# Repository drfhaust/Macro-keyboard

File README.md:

# Macro Keyboard

**Macro Keyboard with ESP32-S3**

This repository contains the design and code for building a custom macro keyboard powered by the ESP32-S3 microcontroller.

## Overview

- **Design**: A macro keyboard with customizable keys and LEDs for different functionalities.
- **Microcontroller**: Powered by the ESP32-S3 with a built-in touch screen and additional hardware components.
- **Customization**: Supports custom key mappings and macros via a JSON configuration.
- **Hardware Design**: The keyboard's hardware is modular, making it adaptable for various input needs.

## Hardware Specifications

- **Microcontroller**: ESP32-S3 with built-in wireless connectivity.
- **Key Components**: Uses Cherry MX-compatible key switches.
- **LEDs**: Individually addressable RGB LEDs for customizable lighting.
- **Screen**: Touch-enabled screen for additional control and feedback.
- **Battery**: Supports external power, and can be adapted for battery-powered use.
- **Charging**: USB Type-C port for charging and data transfer.
- **Connection**: Supports both wired and wireless communication with a host device.

## Software Features

- **Macro Management**: The macros can be configured through the `button.json` file, where each button is assigned a specific action or macro.
- **LED Control**: RGB LEDs can be customized for each button based on the configuration.
- **Key Mapping**: Easily programmable for various applications, from simple shortcuts to complex multi-step macros.
- **Python Integration**: Python scripts are provided to manage macro configurations and interface with the hardware.

## Power Details

- **Power Input**: Powered through USB Type-C or battery.
- **Power Consumption**: Optimized for low power consumption during idle states.

## Repository Structure

- **Arduino code**: Contains the LVGL porting for the ESP32-S3 along with the Arduino source code for the project.
  - `lvgl_Porting`: Core source files for integrating LVGL (LittlevGL) with the ESP32-S3.
  
- **Macro keyboard**: Includes hardware designs, PCB schematics, and component configurations.
  - `GERBER`: Files for manufacturing the PCB.
  - `custom components`: KiCad components for custom parts used in the keyboard.
  - `backups`: Backup files for the PCB designs.

- **python code**: Python scripts to manage macros and configure button functionalities.
  - `macro_manager_v4.py`: Python script for managing the macro functions of the keyboard.
  
- **solidwork 3d**: 3D models of the keyboard parts, including key switches and case designs.
  
- **button.json**: Configuration file where button mappings and LED colors are stored.

## Getting Started

1. **Clone this repository**:
   ```bash
   git clone <repository-url>
   ```

2. **Hardware Setup**: 
   - Flash the ESP32-S3 with the code in `Arduino code/lvgl_Porting`.
   - Assemble the PCB and components according to the schematics in the `Macro keyboard` folder.

3. **Software Setup**:
   - Install the required Python libraries by running:
     ```bash
     pip install -r requirements.txt
     ```

4. **Macro Management**:
   - Configure macros by editing `button.json`.
   - Run the macro manager script to apply your changes:
     ```bash
     python python code/v4/macro_manager_v4.py
     ```

## Contributing

Please read the contribution guidelines before making any changes.

## License

This project is licensed under the MIT License.

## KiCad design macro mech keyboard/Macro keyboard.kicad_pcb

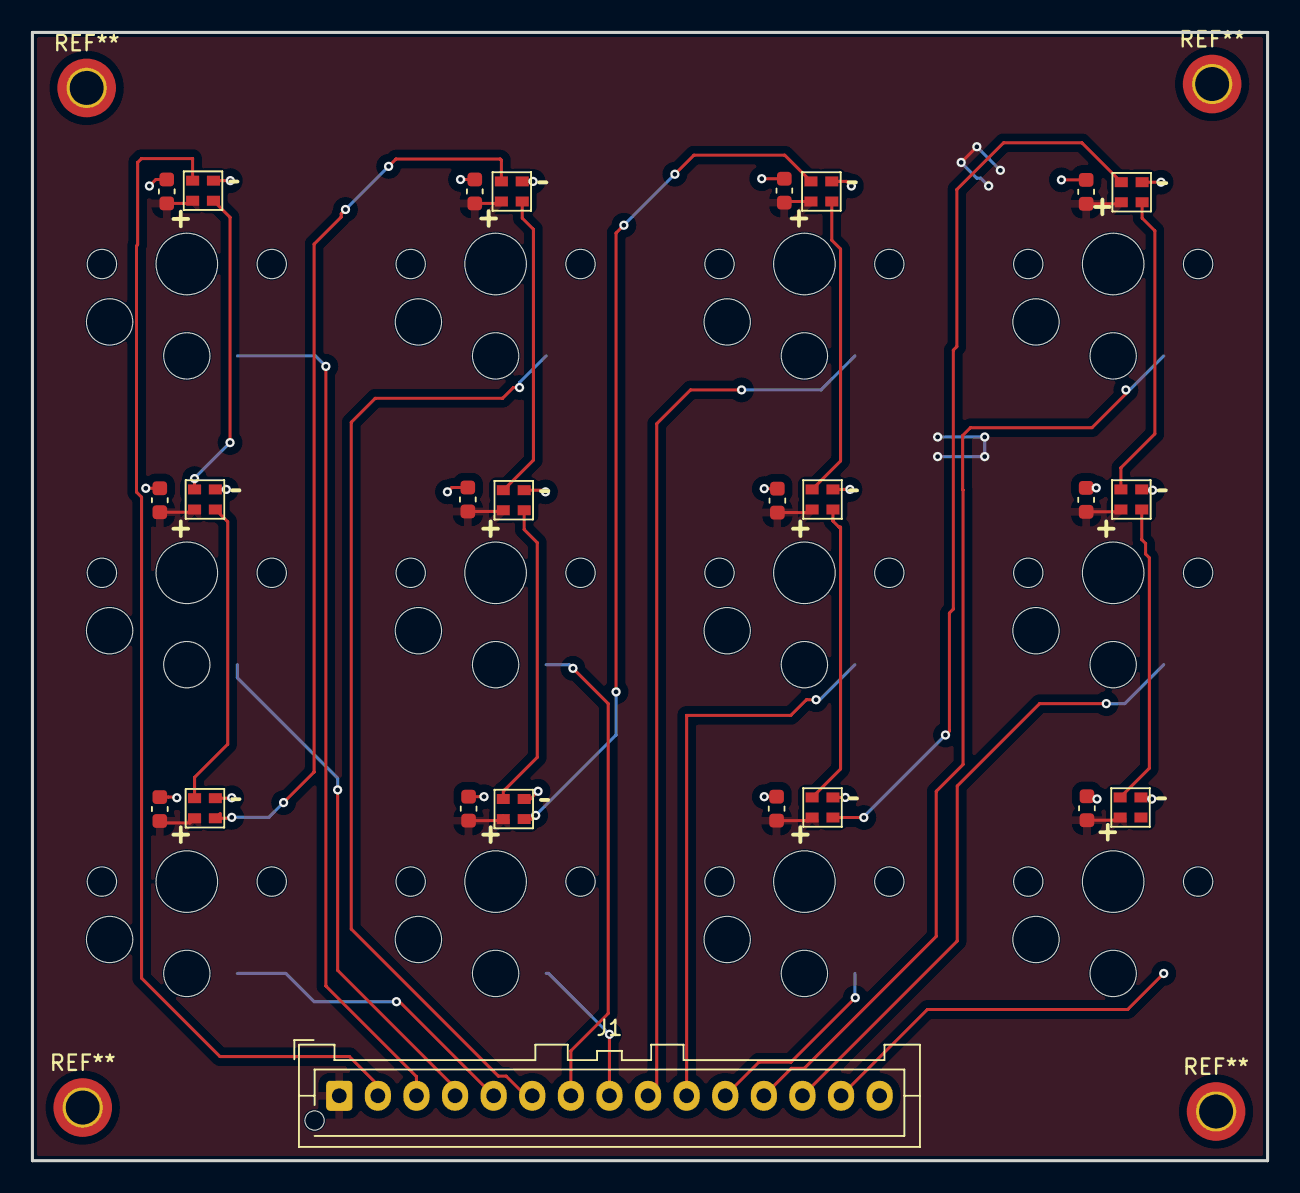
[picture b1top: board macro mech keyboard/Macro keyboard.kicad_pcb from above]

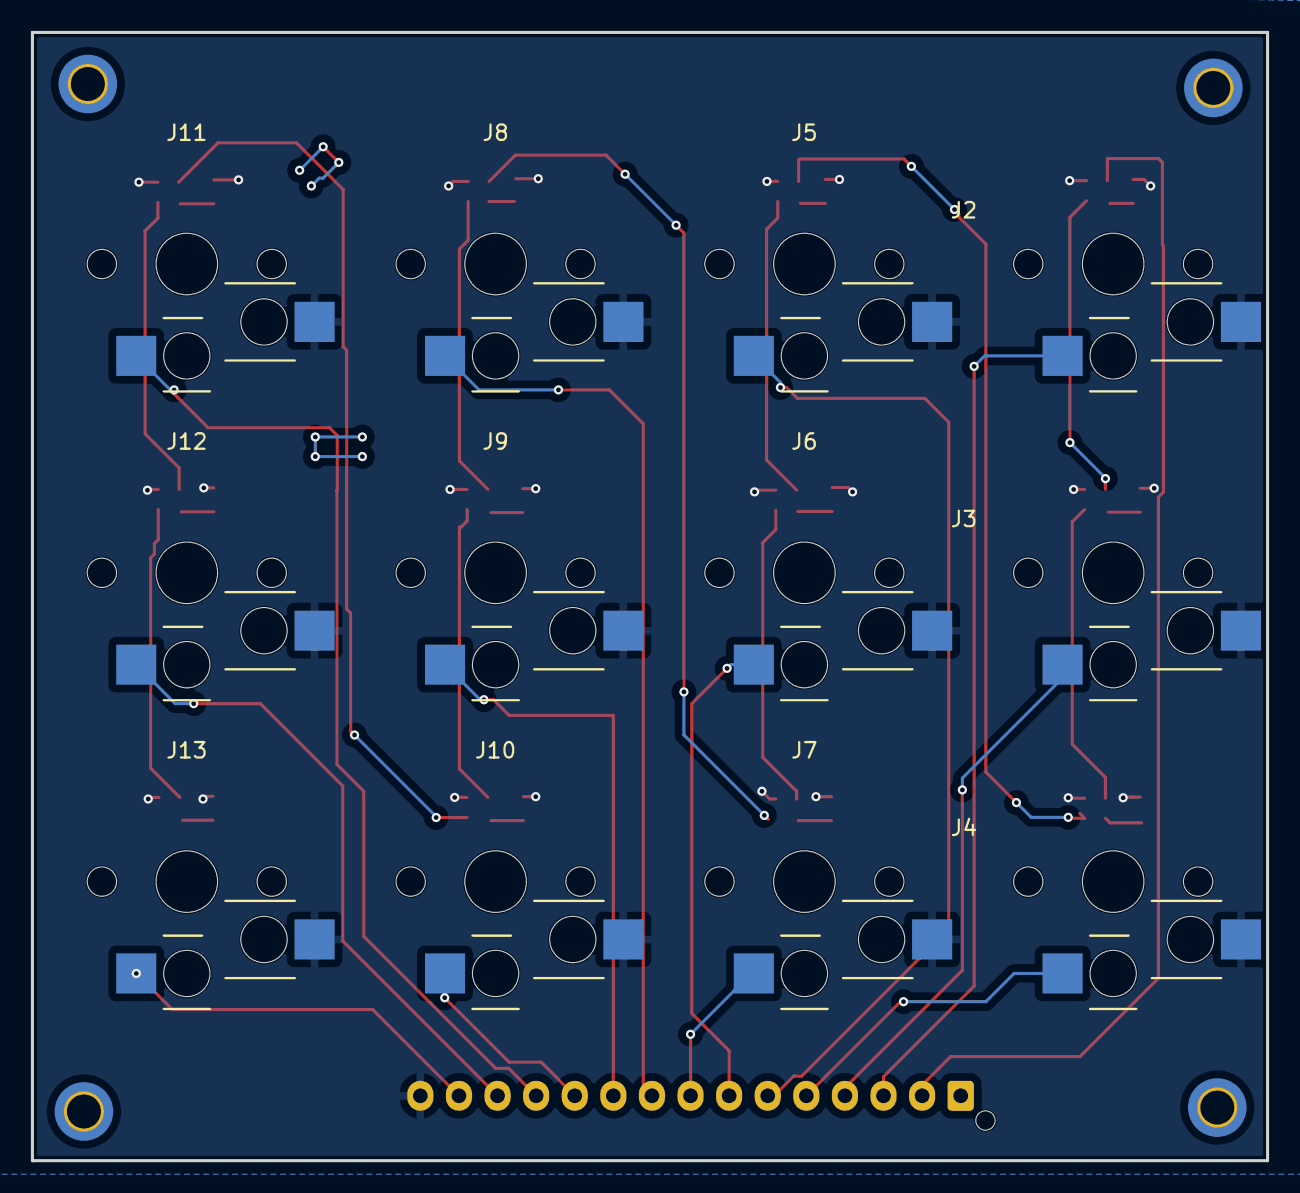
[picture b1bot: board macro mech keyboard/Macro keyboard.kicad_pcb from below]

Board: 2 copper layers, 80.0 x 73.1 mm, 37 parts (12 on the bottom side), 26 nets.

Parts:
C13, C14, C15, C16, C17, C18, C19, C20, C21, C22, C23, C24: 100n; C_0603_1608Metric
D2, D3, D4, D5, D6, D7, D8, D9, D10, D11, D12, D13: RGB; LED_SMD_XINGLIGHT_XL-2020RGBC-WS2812B
J1: Conn_01x15_Pin; JST_XA_B15B-XASK-1-A_1x15_P2.50mm_Vertical
J2, J3, J4, J5, J6, J7, J8, J9, J10, J11, J12, J13: CPG135001S30; Connector_Keyswitch_Socket_KAILH_CPG135001S30

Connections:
+3.3V: C13.1, C14.1, C15.1, C16.1, C17.1, C18.1, C19.1, C20.1, C21.1, C22.1, C23.1, C24.1, D2.4 (vdd), D3.4 (vdd), D4.4 (vdd), D5.4 (vdd), D6.4 (vdd), D7.4 (vdd), D8.4 (vdd), D9.4 (vdd), D10.4 (vdd), D11.4 (vdd), D12.4 (vdd), D13.4 (vdd), J1.1
/BUTTON1: J1.3, J2.1
/BUTTON2: J1.4, J3.1
/BUTTON3: J1.5, J4.1
/BUTTON4: J1.6, J5.1
/BUTTON5: J1.7, J6.1
/BUTTON6: J1.8, J7.1
/BUTTON7: J1.9, J8.1
/BUTTON8: J1.10, J9.1
/BUTTON9: J1.11, J10.1
/BUTTON10: J1.12, J11.1
/BUTTON11: J1.13, J12.1
/BUTTON12: J1.14, J13.1
/RGBLED: D2.3 (di), J1.2
/RGBc: D7.1 (do), D8.3 (di)
GND: C13.2, C14.2, C15.2, C16.2, C17.2, C18.2, C19.2, C20.2, C21.2, C22.2, C23.2, C24.2, D2.2 (gnd), D3.2 (gnd), D4.2 (gnd), D5.2 (gnd), D6.2 (gnd), D7.2 (gnd), D8.2 (gnd), D9.2 (gnd), D10.2 (gnd), D11.2 (gnd), D12.2 (gnd), D13.2 (gnd), J1.15, J2.2, J3.2, J4.2, J5.2, J6.2, J7.2, J8.2, J9.2, J10.2, J11.2, J12.2, J13.2
unnamed: D2.1 (do), D3.3 (di)
unnamed: D3.1 (do), D4.3 (di)
unnamed: D4.1 (do), D5.3 (di)
unnamed: D5.1 (do), D6.3 (di)
unnamed: D6.1 (do), D7.3 (di)
unnamed: D8.1 (do), D9.3 (di)
unnamed: D9.1 (do), D10.3 (di)
unnamed: D10.1 (do), D11.3 (di)
unnamed: D11.1 (do), D12.3 (di)
unnamed: D12.1 (do), D13.3 (di)

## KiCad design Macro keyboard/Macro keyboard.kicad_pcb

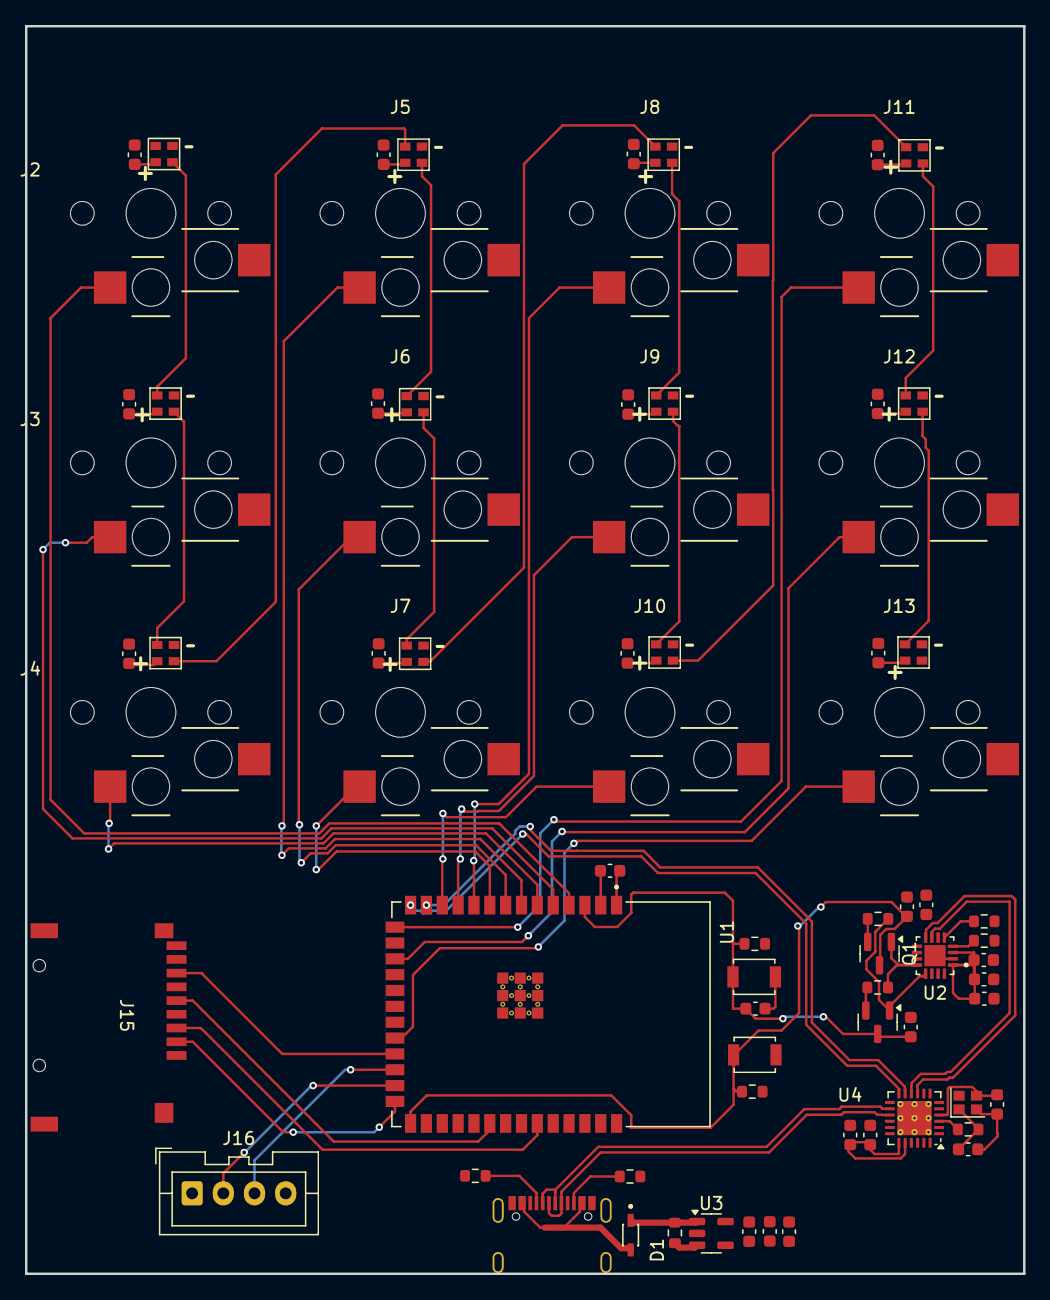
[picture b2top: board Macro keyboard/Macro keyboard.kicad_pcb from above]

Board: 2 copper layers, 80.0 x 100.0 mm, 74 parts (0 on the bottom side), 56 nets.

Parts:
C1, C27: 1uf; C_0603_1608Metric
C2: 4.7uf; C_0603_1608Metric
C3, C4, C5: 100nf; C_0603_1608Metric
C6, C12, C25, C26: 10uf; C_0603_1608Metric
C7, C8, C11: 1UF; C_0603_1608Metric
C9, C10: 15pf; C_0603_1608Metric
C13, C14, C15, C16, C17, C18, C19, C20, C21, C22, C23, C24: 100n; C_0603_1608Metric
D1: B5819WS-TP; SOD2512X115N
D2, D3, D4, D5, D6, D7, D8, D9, D10, D11, D12, D13: RGB; LED_SMD_XINGLIGHT_XL-2020RGBC-WS2812B
J1: MC-126D-DG10; Connector_USB-C_HANBO-ELECTRONIC_MC-126D-DG10
J2, J3, J4, J5, J6, J7, J8, J9, J10, J11, J12, J13: CPG135001S30; Connector_Keyswitch_Socket_KAILH_CPG135001S30
J15: GT-TF003-H0185-02; Connector_MicroSD_G-SWITCH_GT-TF003-H0185-02
J16: Conn_01x04_Pin; JST_XA_B04B-XASK-1_1x04_P2.50mm_Vertical
Q1, Q2: S8050; SOT-23
R1, R2: 12k; R_0603_1608Metric
R3: 100K; R_0603_1608Metric
R5, R6: 0R; R_0603_1608Metric
R7, R8: 5k1; R_0603_1608Metric
R10: 1k; R_0603_1608Metric
R11, R12: 10k; R_0603_1608Metric
SW1, SW2: SW_Push; SW_SPST_B3U-1000P
U1: ESP32-S3-WROOM-1-N8R8; XCVR_ESP32S3WROOM1N8R8
U2: CH343P; QFN50P300X300X80-17N
U3: AP2112K-3.3; SOT-23-5
U4: QFN-24-1EP_4x4mm_P0.5mm_EP2.75x2.75mm_ThermalVias
Y1: Crystal_GND24; Crystal_SMD_2016-4Pin_2.0x1.6mm

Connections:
+3.3V: C3.1, C4.1, C5.1, C7.1, C8.1, C12.1, C13.1, C14.1, C15.1, C16.1, C17.1, C18.1, C19.1, C20.1, C21.1, C22.1, C23.1, C24.1, C25.1, C26.1, C27.1, D2.4 (vdd), D3.4 (vdd), D4.4 (vdd), D5.4 (vdd), D6.4 (vdd), D7.4 (vdd), D8.4 (vdd), D9.4 (vdd), D10.4 (vdd), D11.4 (vdd), D12.4 (vdd), D13.4 (vdd), J16.4, R11.2, R12.2, U1.2 (3V3), U2.1 (VIO), U2.3 (VDD5), U2.6 (V3), U3.5 (VOUT), U4.19 (V5), U4.20 (VDD33)
+5V: C6.1, D1.C, R3.1, U2.9 (VBUS), U3.1 (VIN)
/BUTTON1: J2.1, U1.4 (IO4)
/BUTTON2: J3.1, U1.5 (IO5)
/BUTTON3: J4.1, U1.6 (IO6)
/BUTTON4: J5.1, U1.7 (IO7)
/BUTTON5: J6.1, U1.8 (IO15)
/BUTTON6: J7.1, U1.9 (IO16)
/BUTTON7: J8.1, U1.10 (IO17)
/BUTTON8: J9.1, U1.11 (IO18)
/BUTTON9: J10.1, U1.12 (IO8)
/BUTTON10: J11.1, U1.15 (IO3)
/BUTTON11: J12.1, U1.17 (IO9)
/BUTTON12: J13.1, U1.22 (IO14)
/D+: J1.A6 (D+), J1.B6 (D+), U4.15 (DPU)
/D-: J1.A7 (D-), J1.B7 (D-), U4.14 (DMU)
/DTR: Q1.1 (E), R1.2, U2.12 (DTR)
/MISO: J15.7 (DAT0), U1.23 (IO21)
/MOSI: J15.3 (CMD), U1.35 (IO42)
/RGBLED: D2.3 (di), U1.31 (IO38)
/RGBc: D7.1 (do), D8.3 (di)
/RTS: Q2.1 (E), R2.2, U2.13 (RTS)
/SCK: J15.5 (CLK), U1.32 (IO39)
/SD/CS: J15.2 (DAT3/CD), U1.26 (IO45)
/espD+: U1.14 (IO20), U4.12 (DP1)
/espD-: U1.13 (IO19), U4.11 (DM1)
/uartD+: U2.7 (UD+), U4.10 (DP2)
/uartD-: U2.8 (UD-), U4.9 (DM2)
EN: C2.1, C11.1, Q2.3 (C), R11.1, SW1.2, U1.3 (EN)
GND: C1.1, C2.2, C3.2, C4.2, C5.2, C6.2, C7.2, C8.2, C9.2, C10.2, C11.2, C12.2, C13.2, C14.2, C15.2, C16.2, C17.2, C18.2, C19.2, C20.2, C21.2, C22.2, C23.2, C24.2, C25.2, C26.2, C27.2, D2.2 (gnd), D3.2 (gnd), D4.2 (gnd), D5.2 (gnd), D6.2 (gnd), D7.2 (gnd), D8.2 (gnd), D9.2 (gnd), D10.2 (gnd), D11.2 (gnd), D12.2 (gnd), D13.2 (gnd), J1.A1 (GND), J1.A12 (GND), J1.B1 (GND), J1.B12 (GND), J1.S1 (SHIELD), J2.2, J3.2, J4.2, J5.2, J6.2, J7.2, J8.2, J9.2, J10.2, J11.2, J12.2, J13.2, J15.6 (VSS), J15.10 (SHIELD), J16.1, R7.1, R8.2, SW1.1, SW2.1, U1.1 (GND), U1.40 (GND), U1.41_1 (GND), U1.41_2 (GND), U1.41_3 (GND), U1.41_4 (GND), U1.41_5 (GND), U1.41_6 (GND), U1.41_7 (GND), U1.41_8 (GND), U1.41_9 (GND), U2.2 (GND), U2.17 (GND), U3.2 (GND), U4.25 (GND), Y1.2, Y1.4
Io0: C1.2, Q1.3 (C), R12.1, SW2.2, U1.27 (IO0)
unnamed: C9.1, R10.2, Y1.1
unnamed: D1.A, J1.A4 (VBUS), J1.A9 (VBUS), J1.B4 (VBUS), J1.B9 (VBUS)
unnamed: D2.1 (do), D3.3 (di)
unnamed: D3.1 (do), D4.3 (di)
unnamed: D4.1 (do), D5.3 (di)
unnamed: D5.1 (do), D6.3 (di)
unnamed: D6.1 (do), D7.3 (di)
unnamed: D8.1 (do), D9.3 (di)
unnamed: D9.1 (do), D10.3 (di)
unnamed: D10.1 (do), D11.3 (di)
unnamed: D11.1 (do), D12.3 (di)
unnamed: D12.1 (do), D13.3 (di)
unnamed: J1.A5 (CC1), R7.2
unnamed: J1.B5 (CC2), R8.1
unnamed: J16.2, U1.25 (IO48)
unnamed: J16.3, U1.24 (IO47)
unnamed: Q1.2 (B), R2.1
unnamed: Q2.2 (B), R1.1
unnamed: R5.1, U2.5 (RXD)
unnamed: R6.2, U2.4 (TXD)
unnamed: R3.2, U3.3 (EN)
unnamed: C10.1, U4.4 (XI), Y1.3
unnamed: R10.1, U4.3 (XO)
RXD: R6.1, U1.36 (RXD0)
TXD: R5.2, U1.37 (TXD0)

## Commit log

2024-09-22 push code
2024-10-15 push v3
